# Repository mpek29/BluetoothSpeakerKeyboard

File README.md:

# 🎵 BluetoothSpeakerKeyboard

## 🚀 Overview

**Bluetooth Speaker Keyboard** is a minimalistic open-source PCB designed to provide simple control functionalities for Bluetooth speakers. The board features essential buttons for **volume control**, **Bluetooth pairing**, and **play/pause functionality**. It follows the **Adafruit-compatible footprint**, making it easy to integrate into existing projects.

## 🎯 Purpose
- 🔊 **Seamless audio control**: Easily manage volume, pairing, and playback.
- 🎛️ **Compact and efficient**: Designed for integration with Bluetooth speaker systems.
- 🛠️ **Open-source and customizable**: Modify the design to fit your specific needs.
- 🔌 **Adafruit-compatible**: Fits within Adafruit's standard PCB footprint for easy use in DIY projects.

## 📝 Features
| 🏷️ Feature        | 🔍 Description |
|----------------|-------------|
| 🔉 **Volume Control** | Adjust the speaker's volume up and down |
| 🔄 **Play/Pause Button** | Start or stop the music playback |
| 🔵 **Bluetooth Pairing Button** | Activate pairing mode for easy device connection |
| 🔧 **Minimalist Design** | Only essential components for simplicity |
| 🖥️ **PCB Design** | Open-source & customizable |
| 🌍 **Use Cases** | Embedded in DIY Bluetooth speakers, home automation systems |
| 🔌 **Adafruit-Compatible** | Follows Adafruit's standard PCB footprint |

## 📐 PCB Design Preview
| 📜 Schematic | 🖥️ PCB Layout | 🏗️ 3D |
|-----------|-----------|-----------|
|  |  |  |

## 🌟 License
This project is open-source. Feel free to use, modify, and contribute! 🚀

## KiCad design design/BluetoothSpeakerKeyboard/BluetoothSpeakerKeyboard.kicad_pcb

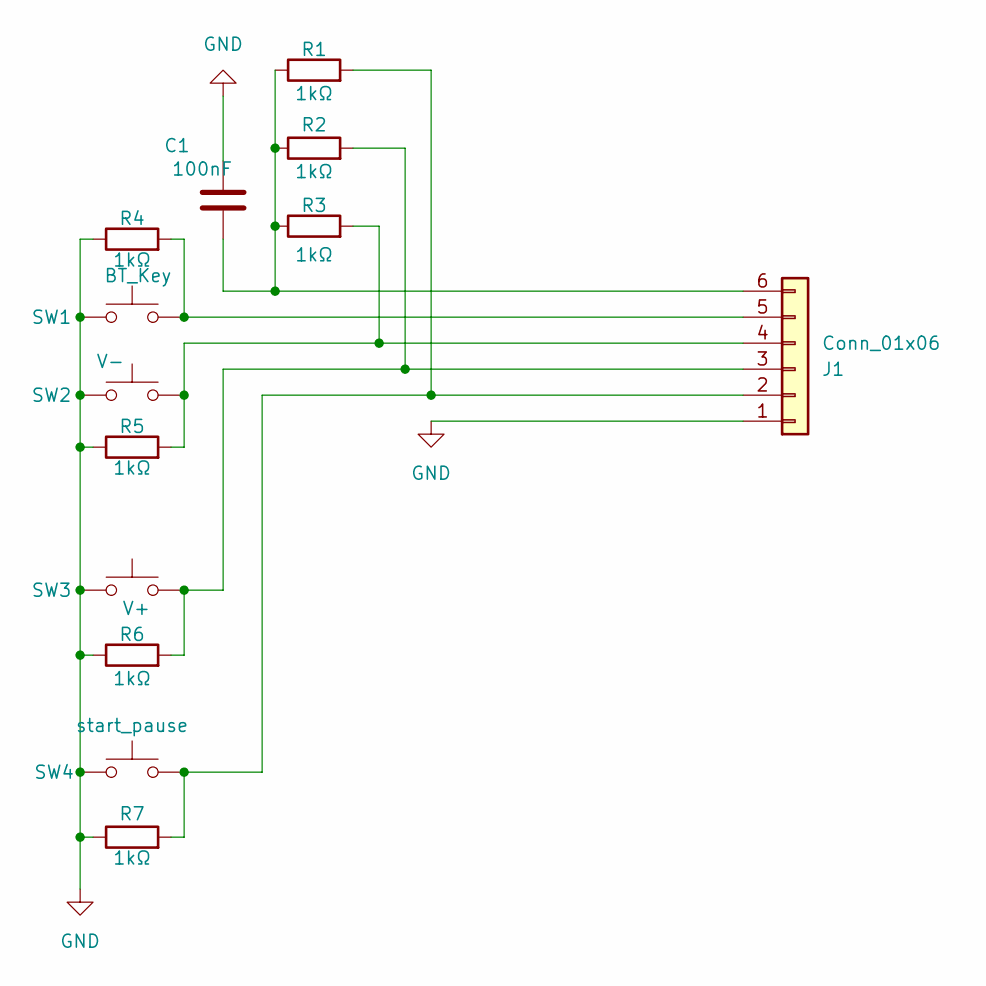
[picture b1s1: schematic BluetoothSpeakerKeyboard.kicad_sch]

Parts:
C1: 100nF; C_0603_1608Metric_Pad1.08x0.95mm_HandSolder
J1: Conn_01x06; JST_SH_SM06B-SRSS-TB_1x06-1MP_P1.00mm_Horizontal
R1, R2, R3, R4, R5, R6, R7: 1kΩ; R_0402_1005Metric_Pad0.72x0.64mm_HandSolder
SW1: BT_Key; SW_Push_1P1T_XKB_TS-1187A
SW2: V-; SW_Push_1P1T_XKB_TS-1187A
SW3: V+; SW_Push_1P1T_XKB_TS-1187A
SW4: start_pause; SW_Push_1P1T_XKB_TS-1187A

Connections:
GND: C1.1, J1.1, R4.1, R5.1, R6.1, R7.1, SW1.1, SW2.1, SW3.1, SW4.1
unnamed: J1.2, R1.2, R7.2, SW4.2
unnamed: J1.3, R2.2, R6.2, SW3.2
unnamed: J1.4, R3.2, R5.2, SW2.2
unnamed: J1.5, R4.2, SW1.2
unnamed: C1.2, J1.6, R1.1, R2.1, R3.1

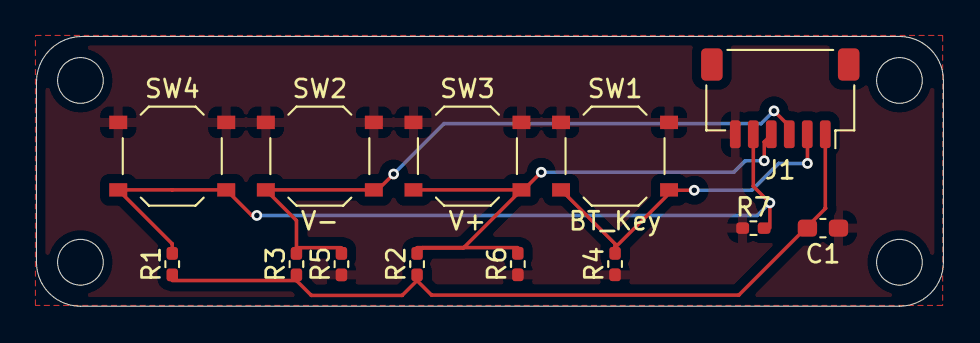
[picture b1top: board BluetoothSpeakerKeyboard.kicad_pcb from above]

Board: 2 copper layers, 50.4 x 15.0 mm, 13 parts (0 on the bottom side), 6 nets.

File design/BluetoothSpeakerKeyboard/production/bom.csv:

Designator,Footprint,Quantity,Value,LCSC Part #
C1,0603,1,100nF,
J1,JST_SH_SM06B-SRSS-TB_1x06-1MP_P1.00mm_Horizontal,1,Conn_01x06,
"R1, R2, R3, R4, R5, R6, R7",0402,7,1kΩ,
SW1,SW_Push_1P1T_XKB_TS-1187A,1,BT_Key,
SW2,SW_Push_1P1T_XKB_TS-1187A,1,V-,
SW3,SW_Push_1P1T_XKB_TS-1187A,1,V+,
SW4,SW_Push_1P1T_XKB_TS-1187A,1,start_pause,

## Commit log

2025-04-10 adjustement and gerber files
